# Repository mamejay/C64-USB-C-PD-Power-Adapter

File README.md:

# C64 USB-C PD Power Adapter

A compact replacement power supply for the Commodore 64. It plugs straight into the C64's 7-pin DIN power socket and runs from any USB-C Power Delivery charger that offers 15 V.

**Status: v0.3 built and tested — working on a real C64.** Measured with the C64 running: 5.07 V on pins 4/5, 12.3 V on pin 6 (12.3 V with no load as well).

**v0.3 (cost-down):**
- All passives are 0603 JLC Basic parts.
- The TVS diodes are JLC Preferred parts.
- Both bucks share one inductor (FXL0530).
- The PTC fuses became 0R links. The 1206 footprints still take a PTC if you want one.
- 5 V feedback is now 75k/10k (5.07 V).
- Extended parts went from 15 to 4: CH224A, TPS54302, USB-C, inductor.

## What it does
| Output | DIN pin | Source |
|---|---|---|
| +5.07 V, up to 3 A | 4, 5 | TPS54302 buck (U2) |
| +12.3 V DC, ~1 A | 6 (the C64's "9 VAC" input) | TPS54302 buck (U3) |
| GND | 1, 2, 3, 7 | |

- **PD sink:** a WCH CH224A requests 15 V from the charger (R1 = 56k).
- **Output switch:** a P-MOSFET (Q1) connects the 15 V rail only once the PD contract is made (PG low). Its Miller cap gives a soft ~10 ms ramp.
- **Lockout:** both bucks have an EN-pin UVLO that starts at ~13.2 V. A plain 5 V charger, or one that falls back to 9/12 V, never powers the C64.
- **Protection:** each output has a TVS diode. F1/F2 are 0R links by default; fit 1206 PTCs there if wanted. For proper over-voltage protection see [v0.4](#v04-over-voltage-protection).

### Why 12 V DC on pin 6
The C64 runs its "9 VAC" input through its own bridge rectifier and a 7812 (breadbin) or 7809 (C64C).

- **Stock supply:** 9 VAC peaks at about 12.7 V.
- **12 V DC** matches that peak, so neither the C64 nor any user-port device (pins 10/11) sees more than an original PSU gives.
- **9 V DC** would starve a breadbin's 6581 SID (12 V supply) and drop out a C64C's 7809.
- **To get 9 V anyway:** change R12 to 7.15k (8.9 V).

**Limitations:** the supply is DC only, so the CIA time-of-day clock won't tick, and user-port devices that need real AC won't work. Same as other DC C64 supplies.

## Hardware
- **Board:** 46.1 x 30 mm, 2-layer, GND pours both sides.
- **J2:** a 7-pin DIN (DIN 45329) male plug insert, soldered through the board from the top side.
  - Pins sit on a 7.0 mm circle at 45° spacing, notch at the top.
  - Holes are 1.6 mm with 2.4 mm pads.
  - It is the only hand-soldered part.
- **Assembly:** every SMD part is on the bottom, for single-side JLCPCB assembly.
- **Case:** 2x M2.5 mounting holes are provided for a future case.
- **USB-C:** HRO TYPE-C-31-M-12. Only VBUS/GND/CC are connected; D+/D- are left open, because PD needs only CC.

## Repository
- `Hardware/KiCad/`: KiCad 10 project (schematic, routed PCB, project libraries).
- `Hardware/scripts/`: the generators and routing pipeline:
  - `gen_sch.py`: schematic.
  - `build_v03.py`: board build from the saved placement (`place_v02.json` + `overrides_v03.json`).
  - `add_holes.py`: mounting holes.
  - `set_netclasses.py`, then `autoroute_v02.sh` (Freerouting 2.5.0), then `gnd_pours.py`, then `texts_upright.py`.
  - `make_din_fp.py`: DIN-7 footprint.
  - `make_fab.py`: JLC outputs.
  - The generators rebuild from scratch; don't re-run them over hand edits.
- `Case (3D print)/`: OpenSCAD case (base and lid), STLs and renders. Not yet test-printed; see its README.
- `JLCPCB Output/`: Gerbers zip, BOM, CPL and `ORDER NOTES.txt`.
  - Bottom-side rotation fixes (U1-U3 +90, D1-D3 +180) are already applied. Give the preview a quick check anyway.

## Test results
**Tested OK (first build, Nov 2026):**
- Boots a C64 from a Dell USB-C laptop charger.
- Output voltages hold under load: 5.07 V on pins 4/5, 12.3 V on pin 6.
- The JLC assembly needed no fixes.

**Still to test:**
- SID audio quality and datasette motor speed.
- What the CH224A does with a charger that doesn't offer 15 V (fallback level, PG behaviour).
- Inrush through Q1 into the C64's bulk capacitors.
- Desk/power-switch clearance on breadbin and C64C machines.
- The 3D-printed case (not yet printed).

**Measuring tip:** pin 6 is DC, even though the C64 labels it "9 VAC". Measure it on the meter's **DC** range: on the AC range a meter shows a misleading figure, about 8 V here.

## v0.4: over-voltage protection
[`Hardware v0.4/`](Hardware%20v0.4/) is v0.3 with an eFuse (TI TPS259470A) on each output in place of the F1/F2 links. It is designed and DRC-clean but **not yet built**.
- **+5 V:** cuts the C64 off above 5.70 V; 3.3 A current limit.
- **+12 V (pin 6):** cuts off above 14.2 V; 1.5 A current limit.
- **Shorted converter:** if a buck fails and passes the 15 V input straight through, the C64 is disconnected. Reverse current is blocked too.
- **Same size:** the board, holes and connectors are unchanged, so the same case fits.
- **Cost:** one new extended part (the eFuse, used twice).

## C128 version
See [`C128 Version/`](C128%20Version/) for the Commodore 128 variant (v0.1, not yet built). It has:
- a square 5-pin socket, plugged with a round DIN-8 insert;
- a 5 A SY8205 regulator for +5 V;
- the same USB-PD front end and 12 V rail as this board;
- a TPS25947 eFuse on +5 V with a 5.64 V over-voltage cutoff and a 4.45 A current limit.

## Licence
[CC BY-NC-SA 4.0](LICENSE): **personal and non-commercial use only. Selling boards, kits, assembled units, cases or modified versions is not permitted.**
See [NOTICE.md](NOTICE.md) for the plain-English terms. Commercial use needs a separate written licence from the author.

This is an independent design. The commercial Sordan/RetroJoy adapter and Side Projects Lab's PD-64 (CC BY-NC-ND) were looked at for ideas only. No files or circuitry were copied from either.

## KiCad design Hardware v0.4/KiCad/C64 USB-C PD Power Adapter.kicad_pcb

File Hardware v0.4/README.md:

# C64 USB-C PD Power Adapter v0.4: over-voltage protection

The tested v0.3 board with an over-voltage cutoff on both outputs. The board size (46.1 x 30 mm), mounting holes, DIN-7, USB-C and LED positions are unchanged, so the v0.3 case fits.

**Status: designed, routed and DRC-clean. Not yet built.** The tested design is still v0.3 (the main `Hardware/` folder).

## What changed from v0.3
F1/F2 were 0R links (no protection). They are replaced by two TI TPS259470A eFuses (LCSC C3662799):

| Rail | eFuse | Cuts off above | Back on below | Current limit |
|---|---|---|---|---|
| +5 V (DIN 4/5) | U4 | 5.70 V (R15 75k / R16 20k) | 5.18 V | 3.3 A (R17 1k) |
| +12 V (DIN 6) | U5 | 14.2 V (R20 51k / R21 4.7k) | 12.9 V | 1.5 A (R22 2.2k) |

- **Shorted converter:** if a buck fails and passes the full 15 V input through, its eFuse disconnects the C64 within microseconds. The eFuses are rated for 23 V at their input, so they survive that.
- **Short or overload:** current-limited, with automatic retry.
- **Reverse current** (e.g. from a cartridge or user-port device) is blocked.
- **TVS diodes** D1 (5 V) and D2 (12 V) stay, behind the eFuses, for fast transients.
- **Power LED** now shows that the 5 V eFuse is on.
- **Voltage at the C64:** the 5 V eFuse drops ~0.05 V at 1.5 A, so the C64 sees about 5.0 V.

Every new resistor is a JLC Basic part. The eFuse is the only new extended part (one setup fee covers both).

## Layout notes
- The 5 V path is solid copper (no thin tracks): one area from the buck output to U4, one from U4 to DIN pin 5. The eFuse's IN/OUT pads are 0.3 mm bars only 0.19 mm apart, so a wide track can't reach them.
- Freerouting ignores KiCad copper zones as obstacles, so `power_planes_v04.py` adds no-track rule areas over the 5 V copper before routing. It also pre-draws a few locked links (DIN pin 4 to 5 on the top layer, eFuse GND pins to vias).
- The 12 V eFuse nets are 0.3 mm tracks. That is plenty for the C64's "9 VAC" load.
- L1 is turned round compared with v0.3, so its switch-node pad faces U2. The 5 V output caps C6/C7 are turned to sit on the 5 V copper.

## Files
- `KiCad/`: KiCad 10 project.
- `scripts/`: `gen_sch_v04.py` (schematic), `build_v04.py` + `place_v04.json` (placement), `power_planes_v04.py`, `full_v04.sh` (route, pour, stitch, DRC loop). Also `set_netclasses_v04.py`, `pours_v04.py`, `stitch_gnd.py`, `drop_dangling_vias.py`, `make_fab.py`.
- `JLCPCB Output/`: Gerbers zip, BOM, CPL and `ORDER NOTES.txt`.
- `Docs/`: 3D renders, routing plot, schematic PDF.

**Before ordering:** check the rotation of U4 and U5 in JLC's placement preview (see ORDER NOTES).

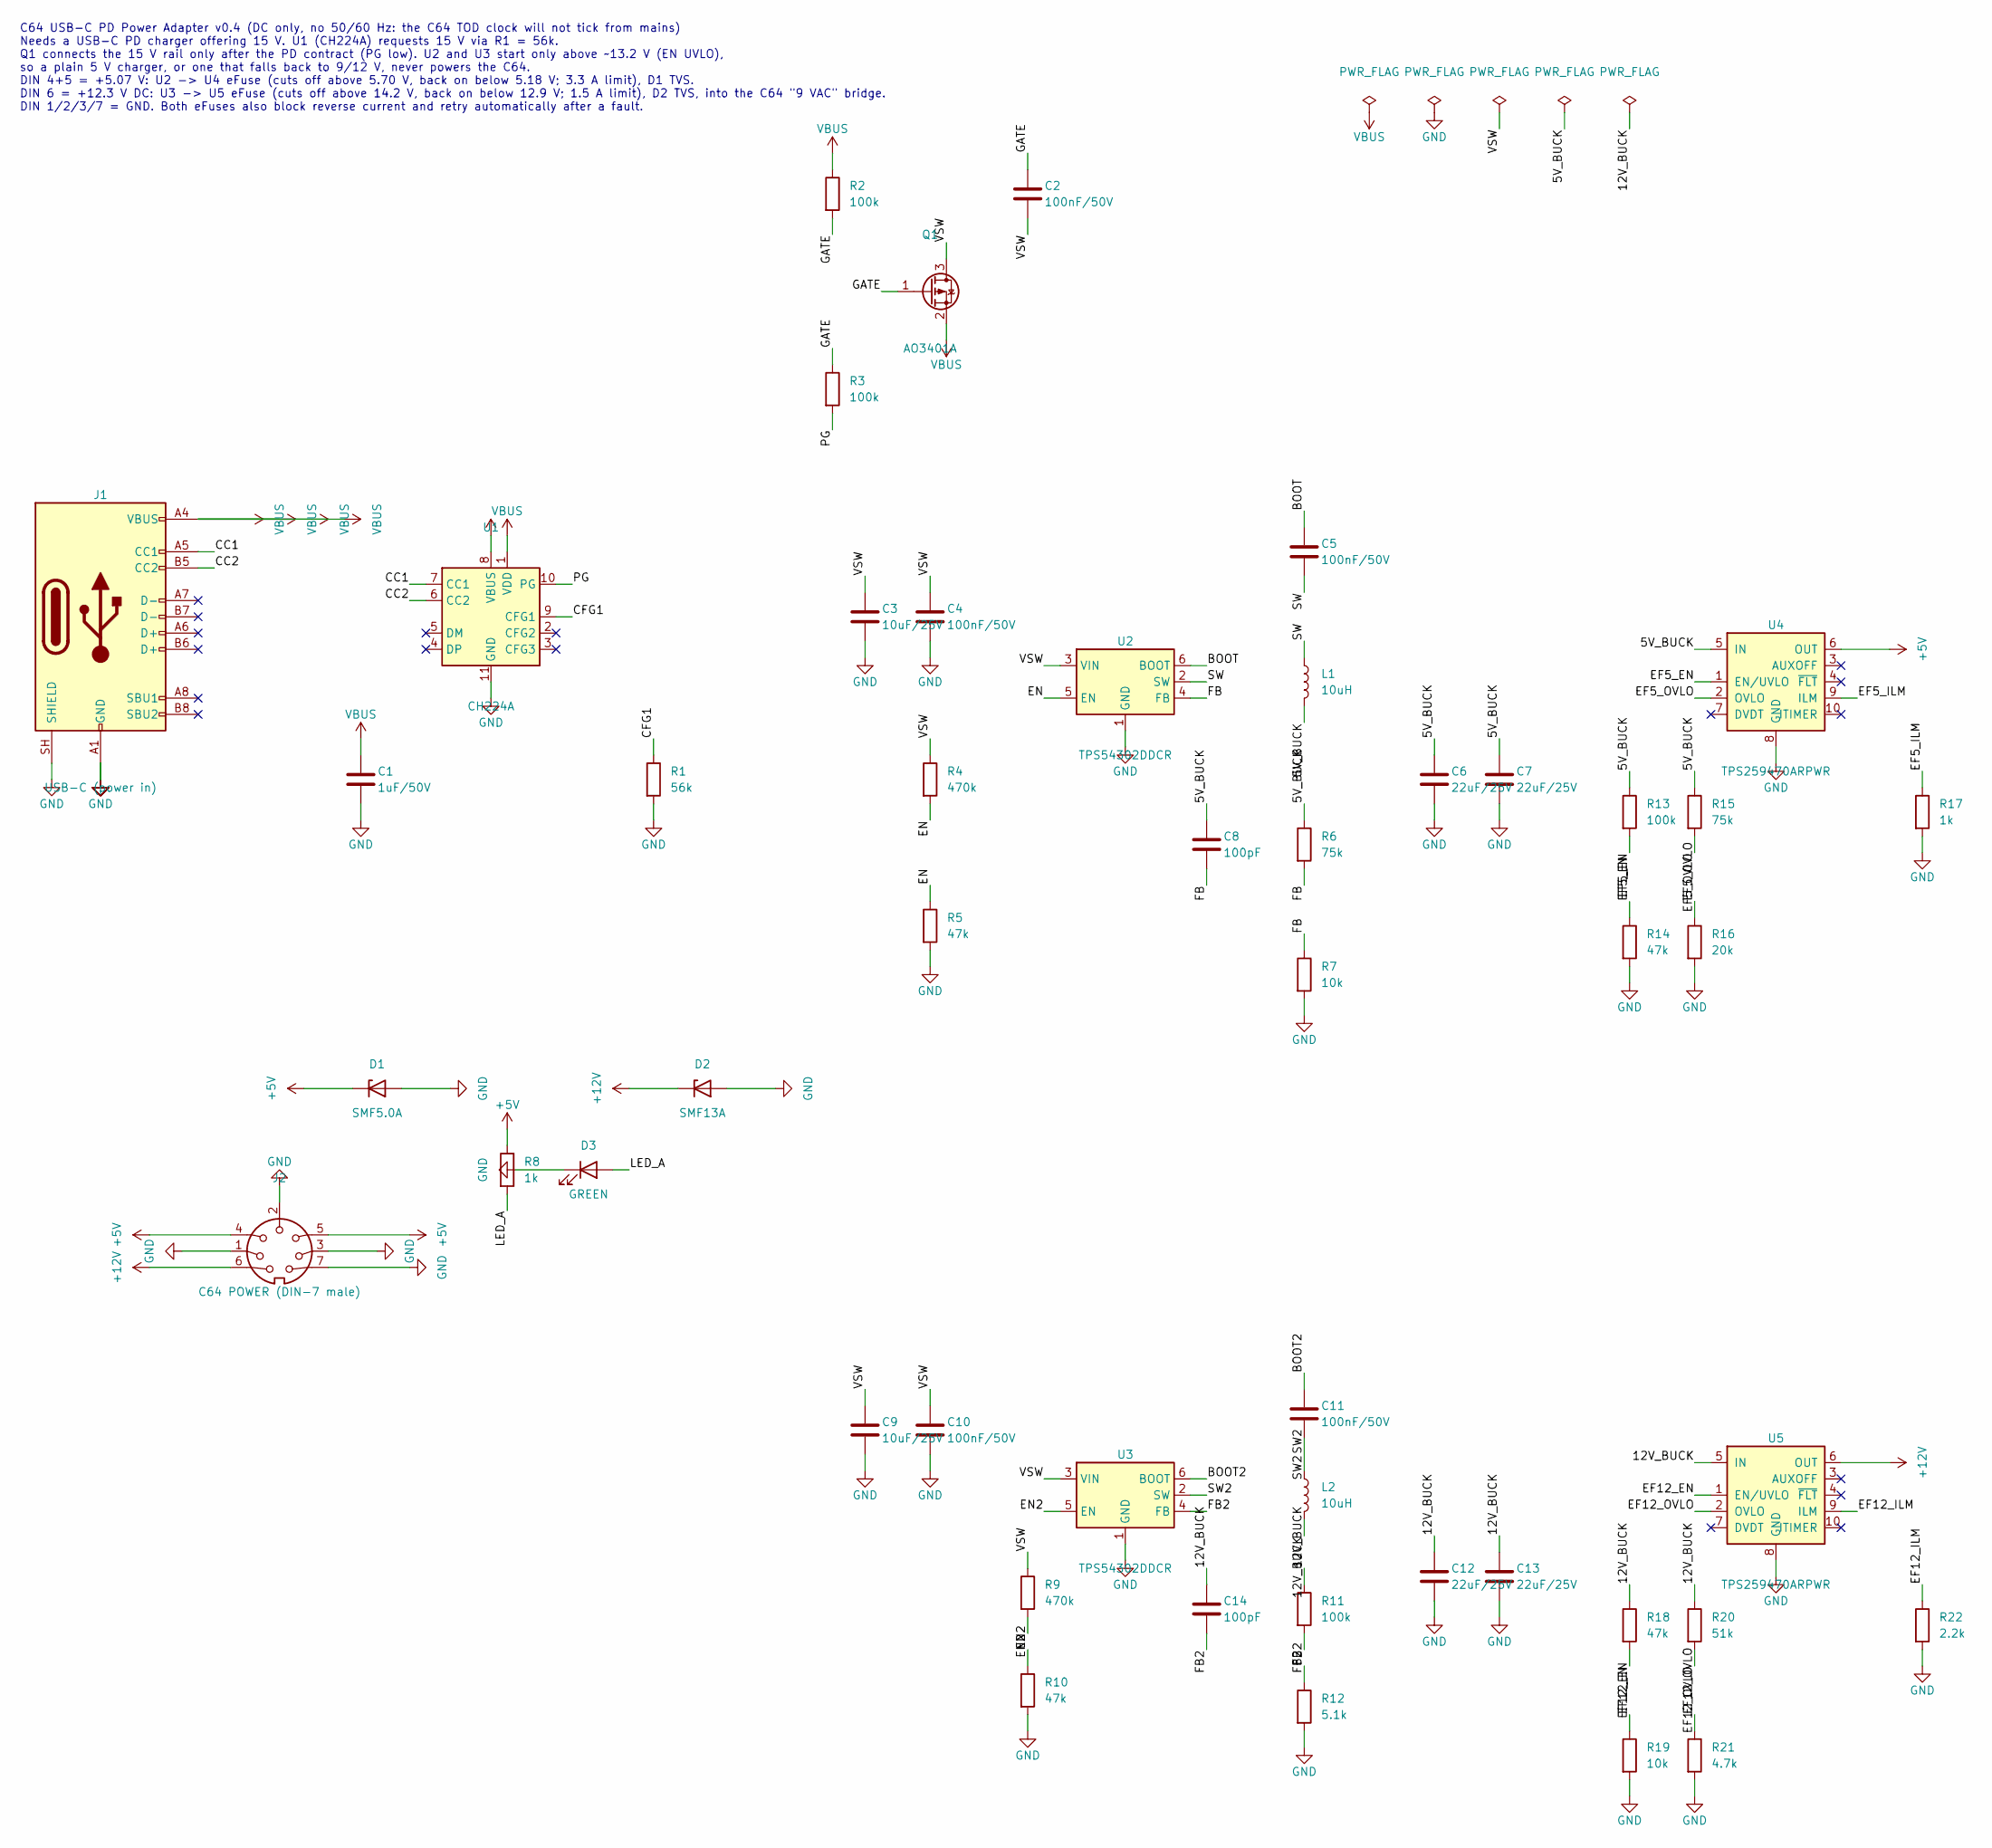
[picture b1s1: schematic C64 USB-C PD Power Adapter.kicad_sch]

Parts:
C1: 1uF/50V; C_0603_1608Metric; LCSC C15849
C2, C4, C5, C10, C11: 100nF/50V; C_0603_1608Metric; LCSC C14663
C3, C9: 10uF/25V; C_0805_2012Metric; LCSC C15850
C6, C7, C12, C13: 22uF/25V; C_0805_2012Metric; LCSC C45783
C8, C14: 100pF; C_0603_1608Metric; LCSC C14858
D1: SMF5.0A; D_SOD-123F; LCSC C19077497
D2: SMF13A; D_SOD-123F; LCSC C41376087
D3: GREEN; LED_0805_2012Metric; LCSC C2297
J1: USB-C (power in); USB_C_Receptacle_HRO_TYPE-C-31-M-12; LCSC C165948
J2: C64 POWER (DIN-7 male); DIN-7_Male_PCB_C64
L1, L2: 10uH; L_Changjiang_FXL0530; LCSC C177248
Q1: AO3401A; SOT-23; LCSC C15127
R1: 56k; R_0603_1608Metric; LCSC C23206
R2, R3, R11, R13: 100k; R_0603_1608Metric; LCSC C25803
R4, R9: 470k; R_0603_1608Metric; LCSC C23178
R5, R10, R14, R18: 47k; R_0603_1608Metric; LCSC C25819
R6, R15: 75k; R_0603_1608Metric; LCSC C23242
R7, R19: 10k; R_0603_1608Metric; LCSC C25804
R8, R17: 1k; R_0603_1608Metric; LCSC C21190
R12: 5.1k; R_0603_1608Metric; LCSC C23186
R16: 20k; R_0603_1608Metric; LCSC C4184
R20: 51k; R_0603_1608Metric; LCSC C23196
R21: 4.7k; R_0603_1608Metric; LCSC C23162
R22: 2.2k; R_0603_1608Metric; LCSC C4190
U1: CH224A; SSOP-10-1EP_3.9x4.9mm_P1mm_EP2.1x3.3mm; LCSC C42459160
U2, U3: TPS54302DDCR; TSOT-23-6; LCSC C311983
U4, U5: TPS259470ARPWR; TI_RPW0010A_VQFN-10-HR_2x2mm; LCSC C3662799

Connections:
+5V: D1.1 (K), J2.4, J2.5, R8.1, U4.6 (OUT)
+12V: D2.1 (K), J2.6, U5.6 (OUT)
/5V_BUCK: C6.1, C7.1, C8.1, L1.2, R6.1, R13.1, R15.1, U4.5 (IN)
/12V_BUCK: C12.1, C13.1, C14.1, L2.2, R11.1, R18.1, R20.1, U5.5 (IN)
/BOOT: C5.1, U2.6 (BOOT)
/BOOT2: C11.1, U3.6 (BOOT)
/CC1: J1.A5 (CC1), U1.7 (CC1)
/CC2: J1.B5 (CC2), U1.6 (CC2)
/CFG1: R1.1, U1.9 (CFG1)
/EF5_EN: R13.2, R14.1, U4.1 (EN/UVLO)
/EF5_ILM: R17.1, U4.9 (ILM)
/EF5_OVLO: R15.2, R16.1, U4.2 (OVLO)
/EF12_EN: R18.2, R19.1, U5.1 (EN/UVLO)
/EF12_ILM: R22.1, U5.9 (ILM)
/EF12_OVLO: R20.2, R21.1, U5.2 (OVLO)
/EN: R4.2, R5.1, U2.5 (EN)
/EN2: R9.2, R10.1, U3.5 (EN)
/FB: C8.2, R6.2, R7.1, U2.4 (FB)
/FB2: C14.2, R11.2, R12.1, U3.4 (FB)
/GATE: C2.1, Q1.1 (G), R2.2, R3.1
/LED_A: D3.2 (A), R8.2
/PG: R3.2, U1.10 (PG)
/SW: C5.2, L1.1, U2.2 (SW)
/SW2: C11.2, L2.1, U3.2 (SW)
/VSW: C2.2, C3.1, C4.1, C9.1, C10.1, Q1.3 (D), R4.1, R9.1, U2.3 (VIN), U3.3 (VIN)
GND: C1.2, C3.2, C4.2, C6.2, C7.2, C9.2, C10.2, C12.2, C13.2, D1.2 (A), D2.2 (A), D3.1 (K), J1.A1 (GND), J1.A12 (GND), J1.B1 (GND), J1.B12 (GND), J1.SH (SHIELD), J2.1, J2.2, J2.3, J2.7, R1.2, R5.2, R7.2, R10.2, R12.2, R14.2, R16.2, R17.2, R19.2, R21.2, R22.2, U1.11 (GND), U2.1 (GND), U3.1 (GND), U4.8 (GND), U5.8 (GND)
VBUS: C1.1, J1.A4 (VBUS), J1.A9 (VBUS), J1.B4 (VBUS), J1.B9 (VBUS), Q1.2 (S), R2.1, U1.1 (VDD), U1.8 (VBUS)

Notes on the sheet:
C64 USB-C PD Power Adapter v0.4 (DC only, no 50/60 Hz: the C64 TOD clock will not tick from mains) Needs a USB-C PD charger offering 15 V. U1 (CH224A) requests 15 V via R1 = 56k. Q1 connects the 15 V rail only after the PD contract (PG low). U2 and U3 start only above ~13.2 V (EN UVLO), so a plain 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

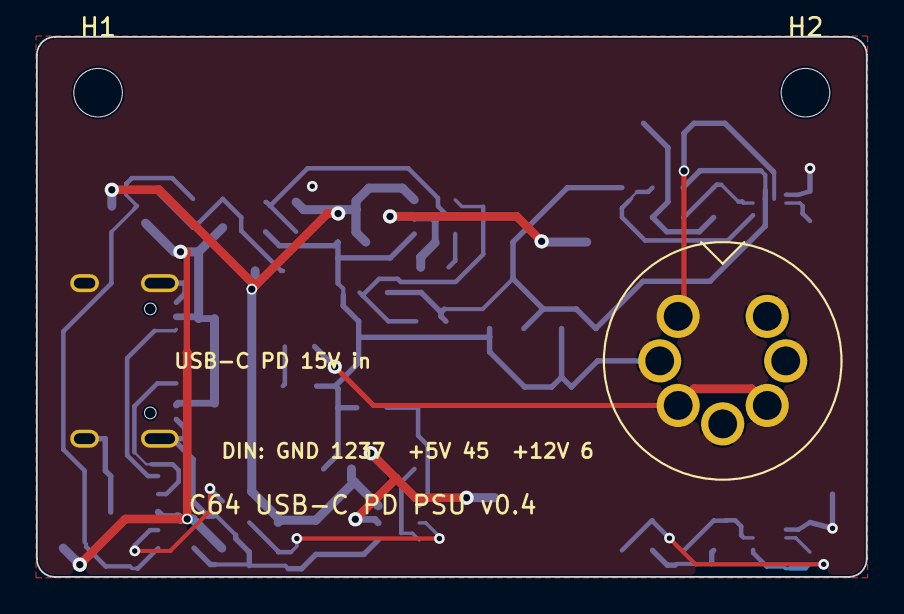
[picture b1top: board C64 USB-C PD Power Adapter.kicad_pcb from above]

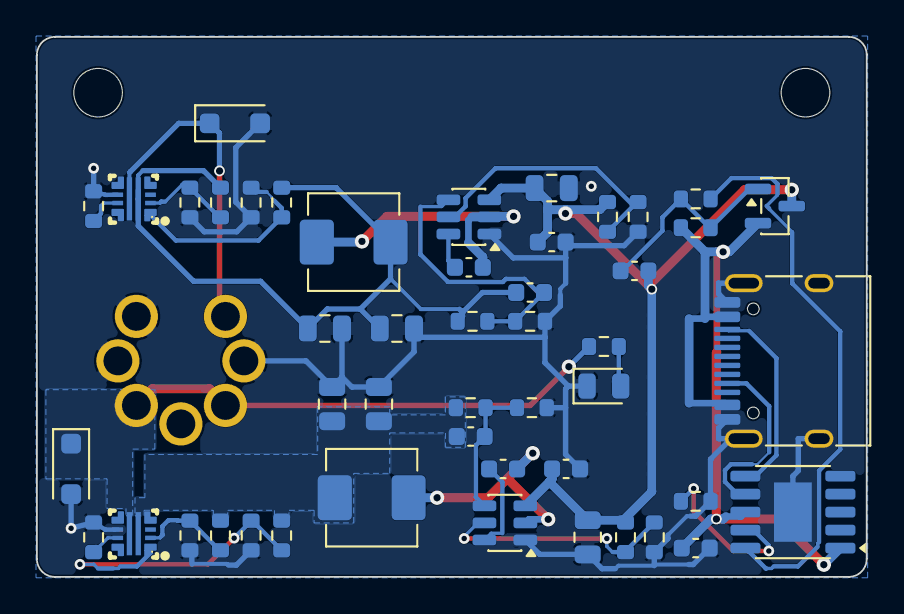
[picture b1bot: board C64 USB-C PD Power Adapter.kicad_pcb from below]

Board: 2 copper layers, 46.1 x 30.0 mm, 51 parts (48 on the bottom side), 27 nets.

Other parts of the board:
H1, H2: M2.5; MountingHole_2.7mm_M2.5

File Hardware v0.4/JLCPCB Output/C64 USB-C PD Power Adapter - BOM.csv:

Comment,Designator,Footprint,LCSC Part #
1uF/50V,C1,0603,C15849
100nF/50V,"C2,C4,C5,C10,C11",0603,C14663
10uF/25V,"C3,C9",0805,C15850
22uF/25V,"C6,C7,C12,C13",0805,C45783
100pF,"C8,C14",0603,C14858
SMF5.0A,D1,SOD-123F,C19077497
SMF13A,D2,SOD-123F,C41376087
GREEN,D3,0805,C2297
USB-C (power in),J1,TYPE-C-31-M-12,C165948
10uH,"L1,L2",FXL0530,C177248
AO3401A,Q1,SOT-23,C15127
56k,R1,0603,C23206
100k,"R2,R3,R11,R13",0603,C25803
470k,"R4,R9",0603,C23178
47k,"R5,R10,R14,R18",0603,C25819
75k,"R6,R15",0603,C23242
10k,"R7,R19",0603,C25804
1k,"R8,R17",0603,C21190
5.1k,R12,0603,C23186
20k,R16,0603,C4184
51k,R20,0603,C23196
4.7k,R21,0603,C23162
2.2k,R22,0603,C4190
CH224A,U1,SSOP-10,C42459160
TPS54302DDCR,"U2,U3",TSOT-23-6,C311983
TPS259470ARPWR,"U4,U5",TI_RPW0010A_VQFN-10-HR_2x2mm,C3662799
